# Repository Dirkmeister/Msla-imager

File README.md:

# Msla-imager

Shared code for the MSLA PCB imager (MSLA PRINTER Claude Project). This index is kept by HQ, in step with the Code home section of imager-00.

- **Folders.** Each folder belongs to one lane, except `calcs/`, where any lane adds its own calc scripts as separate files.
- **One writer per file.** The lane that creates a file owns it and names itself on line 1, or on line 2 under a shebang; other lanes change it through that owner.
- **Commits** start with the package or lane (`L4.2: loader`, `L4: converter v0`). A packet that confirms code cites the commit.

| Folder | Lane | What |
|---|---|---|
| `calcs/` | HQ, plus lane-owned scripts | `imager_calcs.py` (HQ, recovery pending). Lane scripts: `l1_*` (L1 Light engine), `l2_*` (L2 LCD mask) |
| `light/` | L1 Light engine | Cluster and sink board KiCad, stand mounts (not started) |
| `lcd/` | L2 LCD mask | Pi video config and bring-up scripts (`setup_display.sh`, `fbtest.py`, `show_png.py`, `edid_timing.py`; simulation-checked), the 1:1 PNG script until L4 takes it, package records in `lcd/records/` |
| `software/` | L4 Software | Pattern generator, Gerber-to-PNG converter, IF-13 job files; later the Pi app. See `software/README.md` |
| `firmware/` | L3 Controller and safety | Nano firmware (not started) |
| `mech/` | L5 Mechanics | Platen and enclosure CAD, 3018 G-code (not started) |

Plan docs live in the Claude Project (imager-00 to imager-09, IF-13 spec). Run L4 tools from `software/`. Datasheets under copyright (the Sharp LS055R1SX04 spec, for one) stay out of this repo.

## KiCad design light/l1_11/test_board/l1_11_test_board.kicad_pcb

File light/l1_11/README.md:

# L1: L1.11 C optic test: bench procedures, test board, rig

Package L1.11 of lane L1 (imager-09). Tests: T-UV-7 (optic 400 nm efficiency) and T-UV-6 (LED-to-optic height, beam, pointing), then C21 or C28 (imager-06 "C optic and array checks", calc §5 and §6c). This folder holds what the bench needs; the calc scripts and readings sit in `calcs/` (`l1_11_*`).

Rule for every step with a lit LED: the shroud is closed first. Read through the meter, never by eye in the beam (R9). The XL6009 check has no UV.

## 1. XL6009 bench check (no UV)

What it proves: the XL6009 module (B07XG323G8) holds 26.2 V at the C21 strings' 0.55 A from the 12 V brick for 10 min without running hot (calc §8). Readings go in `calcs/l1_11_xl6009.csv`; `python3 calcs/l1_11_xl6009.py` does the math and the pass rules.

On hand: XL6009 module, ALITOVE ALT-1205T brick, the two 24 Ω 50 W loads, Klein MM300 (one meter), Klein IR thermometer, leads.

```
 brick +12 ──(meter, 10 A jack, step 6 only)── IN+ ┌─────────┐ OUT+ ── 24 Ω ── 24 Ω ──┐
 brick GND ─────────────────────────────────── IN- │ XL6009  │ OUT- ──────────────────┘
                                                   └─────────┘
 loads screwed or clamped flat on metal; fingers off: 7.15 W each
```

1. **Cap.** Read the voltage printed on the output electrolytic (the OUT side). Pass: ≥ 35 V. → `cap_out_rating_V`.
2. **Load, cold.** Meter on 200 Ω: touch the probes together (`R_leads_ohm`), then the two loads in series (`R_load_cold_ohm`, about 48).
3. **Set point.** Brick on, no load. Meter on 200 V at OUT; trim the pot to read 26.2 (`V_out_noload_V`). Also note the brick alone on 20 V (`V_brick_noload_V`).
4. **Run.** Power off, connect the 48 Ω load (on metal), power on and start a timer. Meter stays in V mode; move the probes, not the wires:
   - 1 min: OUT on 200 V → `V_out_1min_V`. If it reads under 26.2, trim back to 26.2 now and log the trimmed value instead.
   - 2 min: IN terminals on 20 V → `V_in_2min_V`. 5 min OUT, 6 min IN, 10 min OUT and IN.
   - Watch for a dropout or the output clicking off → `dropout_or_hiccup`.
5. **Temperatures at 10 min.** IR thermometer close in, so the spot covers one part: XL6009 chip, diode, inductor, output cap, each load (the loads' shiny housing reads low: aim at a matte spot or a strip of masking tape). Room temperature at the bench. Pass: hottest module point ≤ 185 °F (85 °C) (EST, proposed).
6. **Input current.** Power off. Meter red lead to the 10 A jack, in series with IN+. Power on, read within 30 s while everything is still hot → `I_in_A`. Power off. Red lead back to the V jack before anything else.
7. Optional: the same in series with OUT+ → `I_out_A` (the script also gets it from V/R).

Expected (EST, calc §8): 0.546 A and 14.30 W out; about 1.40 A in at 12.0 V at 85 %. The meter's 10 A range is ±(3 % + 5 digits), so η comes out about ±0.07: good enough for the record, not a pass rule.

Pass (proposed; the lead confirms): cap ≥ 35 V; 26.2 V with no load; Vout at 10 min within 0.1 V of 1 min with no dropout; hottest module point ≤ 85 °C. A fail puts a CV boost on the buy list with the build optics.

## 2. Test board panel (`test_board/`)

One KiCad 7 file, three boards on one 2-sided 1.6 mm (0.063 in) 1 oz FR4 blank. Panel 86 x 125 mm (3.39 x 4.92 in). On a 4 x 5 in (101.6 x 127 mm) piece that leaves 0.31 in (7.8 mm) a side across but only 0.04 in (1 mm) a side along: (101.6 - 86)/2 and (127 - 125)/2. A 4 x 6 in (101.6 x 152.4 mm) piece leaves 0.54 in (13.7 mm) along for clamping; or cut the test board (86 x 80 mm) from one piece and the two small boards from another. Isolation-milled on the top only, 0.4 mm (15.7 mil) cuts; the bottom copper stays intact as a floating heat spreader. PCB milling on the 3018 isn't set up yet (Dallas, 2026-11-17): the Gerbers wait for it.

- `l1_11_test_board.kicad_pcb` / `.kicad_pro`, footprints in `l1_11.pretty` (project `fp-lib-table`). Regenerate: `python3 light/l1_11/test_board/make_test_board.py` (KiCad 7 pcbnew). No schematic: the board is drawn directly; nets below.
- `gerber/`: F.Cu (isolate), Edge.Cuts (cut out), PTH drill (10 x 0.126 in (3.2 mm), all unplated on a milled board), F.SilkS and F.Fab for reference. B.Cu is empty on purpose: don't mill the bottom.
- `drc_report.txt`: 0 clearance, short or unconnected errors. Left: library warnings (this sandbox has no global footprint table; they clear in your KiCad) and a few silkscreen warnings (no silk on a milled board).

**A. Test board, 86 x 80 mm (3.39 x 3.15 in).** 9 CUN0LF1B at C21's pitch, 0.787 x 0.893 in (20.00 x 22.68 mm), footprint `LED_SMD:LED_PLCC_2835_Handsoldering` (KiCad 7's stock part matches the V1 board @ 8208f05 pad for pad: large pad 1 = K at -1.05 mm, pad 2 = A at +1.525 mm). The strings are the rows, anode on the left: `VIN_Rr | D | Rr_N1 | D | Rr_N2 | D | Rr_OUT`. Each cut runs through an LED's pad gap, so every inner cathode pad sits in a 0.77 x 0.88 in (19.6 x 22.3 mm) island (119.325 - 99.725 by 111.14 - 88.86 for the center LED): most of the copper stays (L1.12 reads FR4's per-LED θ from this board). NTC TH1 (1206) sits on two isolated islands 0.20 in (5 mm) right of the center LED, beside its cathode pad, with two wire pads. No ballasts on this board: their 1.1 W typ would bias L1.12's θ. Holes: 4 x M3 on the ATS's 53.00 mm (2.087 in) square centred on the center LED, 4 x M3 on a 71.0 mm (2.795 in) square for the holder and the rig frame, so the board mounts at 0° or 90° for the two scan axes; each hole has an isolated copper ring under the screw head, so a screw can't join two nets through the ATS.

**B. Control board, 60 x 40 mm, outside the shroud.** Brick +12 V in → three VIN wires. Each string's OUT wire → a link (JP1-3: solder bridge, or clip lead; open it and clip the meter's 200 mA range across to read that string's current; leave it open to switch the string off) → ballast R1-3 → GND. Ballast footprint takes either your 12 Ω ≥ 0.61 W axial laid flat (leads bent to the outer pads) or four 47 Ω 1206 in parallel (11.75 Ω): fit one. Detector load RL across DET A+/K- (1206 or axial, 100 kΩ to start) with meter pads; NTC wire and meter pads.

**C. Detector board, 22 x 36 mm.** The spare CUN0LF1B (D10) as the detector, A+ and K- wire pads, 2 x M3 to the detector carriage.

**Before soldering: polarity.** The footprint (and V1) say the large pad is the cathode; the CUN0LF1B DS drawing isn't readable as text. Two checks, neither powers an LED:
1. Phone macro photos, sent here: a spare from the cut tape, top and bottom; one LED on the populated V1 board with both pads in view (V1 put pad 1 = K on the large pad).
2. Daylight, optional: a spare with fine wires on its pads, 1 MΩ across them, meter on 200 mV, facing a window or outside. A positive reading means the red lead is on the anode.

If the large pad turns out to be the anode, nothing changes on the board: all nine face the same way, so swap the string wires (VIN on the right pads, OUT on the left). The NTC still sits by the large (thermal) pad.

**Assembly.** LEDs from the cut tape, all the same way round (large pad right as drawn). Mill, deburr, clean; paste and hot air or a hot plate, or an iron. TH1 on its two islands; two fine wires off its wire pads, flat on the board, out past the right edge (the holder gets a groove for them). Grease on the ATS, board centred on it, 4 x M3 through the ATS's corner holes (caliper them first, and the ATS base thickness, for the screw length); nuts between the fins.

| Wire | From | To |
|---|---|---|
| VIN1-3 | control V12 pads | test board VIN1-3 (left edge) |
| OUT1-3 | test board OUT1-3 (right edge) | control S1-S3 OUT pads |
| NTC x2 | TH1 wire pads | control NTC pads |
| DET x2 | detector A+, K- | control DET A+, K- |
| Brick | +12 and GND | control +12 IN, GND IN |

At the brick's 12.0 V each string runs 125-225 mA across the Vf bins, 175 mA typ, through 12 Ω; ballast 0.61 W max (calcs/l1_c_lead_checks.py section 6, EST). With 4 x 47 Ω (11.75 Ω) the top bin reaches (12.0 - 3 x 3.1)/11.75 = 230 mA, still under the DS's 250 mA.

## 3. Rotation rig (`rig/`)

Dallas picked the turntable over the hand-moved slide (2026-11-17): the board turns under a knob on the shroud lid, the detector stays put, and the shroud never opens during a scan. The axis runs through the center optic's exit face. It replaces imager-06's linear detector scan (proposed to the lead in the packet).

`l1_11_rig.scad` (OpenSCAD 2021.01, parametric) → `sh export.sh` writes `stl/` (binary STL) and the picture. Every part fits the MK3S+ bed (250 x 210 x 210 mm); the largest is a track segment at 226 x 44 mm.

| Part | Qty | Filament | Notes |
|---|---|---|---|
| `base` | 1 | black PLA | 150 x 150 mm; pivot boss, sockets for track 1 |
| `rotor` | 1 | black PLA | Ø140 mm, rim ticks every 5°; nut traps underneath |
| `frame` | 1 | black PETG or ASA | holds the board on its 71.0 mm hole square at 0° or 90°; the ATS passes through; the top arm carries the shaft. Next to warm parts, so not PLA |
| `shaft` | 1 | any | 10 mm square, prints 6.30 in (160 mm): cut from the top end to L = box inside height + lid thickness − 99 mm |
| `knob` | 1 | any | pointer reaches the scale's ticks |
| `scale` | 1 | any | Ø140 mm, 1° ticks, labels every 10° from −170 to 180; tape it to the lid |
| `track1`, `track2` | 1 each | black PLA | dovetail rib, joined by dovetail tabs (no screws); mm from the axis engraved; detents at 4, 12 and 18 in |
| `carriage` | 1 | black PLA | rides the rib; lock screw into the detents; post for the detector board |

Black inside the shroud keeps stray UV off the detector. Prints: 0.2 mm layers, 3 perimeters, 20-30 % infill, no supports (the frame prints on its back face; the carriage upright).

**Hardware (M3, from stock; check the lengths you have):**
- Frame foot to rotor: 2 x M3 x 14, nuts in the rotor's underside. The screw tip must not stick out below the rotor.
- Board to frame: 4 x M3 x 10 with no holder (board + frame = 7.6 mm); longer once the holder goes on (its thickness comes with its drawing). Nuts in the frame's back face.
- Board to ATS: 4 x M3, length = 1.6 mm + the ATS base thickness + a nut (caliper the base).
- Shaft pin: 1 x M3 x 16 through the arm into the shaft. Knob set screw: 1 x M3 x 10.
- Carriage lock: 1 x M3 x 10 down into a detent. Detector board: 2 x M3 x 10.

**Assembly.** Base on the shroud floor. Rotor over the boss. Board plus ATS onto the frame (4 corner screws), frame onto the rotor through the foot slots: slide it until the center optic's exit face sits over the boss, then tighten. Shaft into the arm, pinned. Tracks into the base's sockets. Carriage on the rib from the far end, the detector board on its post facing the board. Lid on, knob on the shaft, set screw. With the board square to the track (rotor 0 tick at the base's index), turn the scale until the pointer reads 0 and tape it down.

**Shroud (yours to build: cardboard box or foam board).** Inside at least 24 x 12 x 8 in (610 x 305 x 203 mm): the rig runs from the base's back edge at -75 mm to the track's end at +495 mm, 570 mm, plus 10 mm at the back wall = 580 mm (22.8 in). Lid: one Ø1.42 in (36 mm) hole over the boss, 3.35 in (85 mm) from the back wall, centred across; the knob's skirt covers it. One small hole low in a side wall for the 10 wires. Matte black inside if you can: wall reflections show up as false tails in the profile. A background reading with the beam turned away (±150°) measures what's left.

**Waits for the optics.** The holder plate, the black blanks (they block a lit LED's pocket) and the 0.010 in (0.25 mm) shims. No public 20XPS drawing turned up (LEDSupply lists Ø20 x 8.5 mm only), so the holder gets drawn from calipers when they land. Measure on one optic: overall diameter and height; any rim or flange, its diameter and thickness; the bottom face diameter; the entrance cavity's diameter and depth; any legs or pins. Plus the height of a spare 3528 off the tape. A side-on and a bottom-up phone photo helps. The frame's foot slots take ±0.47 in (±12 mm) of exit-face height, so the holder can come out at whatever height the optic needs.

## 4. T-UV-7: optic efficiency at 400 nm (first; go/no-go)

Readings sheet: `calcs/l1_11_optic_readings.csv`, written in bench order by `python3 calcs/l1_11_optic_test.py --skeleton`, with every dial angle filled in. Fill only the `reading` column; `python3 calcs/l1_11_optic_test.py` does the rest (with no readings yet it runs its self-test on synthetic scans).

Method (proposed, replaces imager-06's linear scan): the board turns, the detector stays at D = 4.00 in (101.6 mm). Flux through the sphere about the axis, Φ = 2π D² ∫ E(φ) sin φ dφ, from the mean of four half-profiles (two axes, both sides). η = Φ_optic / Φ_bare, three passes. Both are integrated, so the bare LED doesn't need to be Lambertian.

1. **Setup.** Shroud closed for every reading. Detector wired to the control board's DET pads, RL = 100 kΩ across them, meter on 200 mV (2000 mV for the optic's peak). String 2 only: link S2 bridged, S1 and S3 open. That lights D4, D5 and D6; D5 is the center LED on the axis. During optic passes, D4 and D6 carry black blanks.
2. **Range check, once, before pass 1.** Optic on D5, dial at 0, LED settled (step 3). Pick RL so this peak reads 200-500 mV: start at 100 kΩ, go up if it's under 200, down if it's over 500. Above about 0.5 V the detector starts to forward-bias itself and stops being linear (EST). The bare LED then reads about 1/23 of the peak (the self-test's on-axis gain at 4 in), about 9-22 mV, still 90-220 counts on the 200 mV range. Keep that RL for the whole session: every result is a ratio.
3. **Settle.** After each power-up, wait until the on-axis reading holds within 1 % for a minute (EST 2-3 min) before scanning. Each scan starts with a dark reading (UV off).
4. **Scans** (the sheet lists every angle): bare from −85° to +85° every 5° (35 readings); optic every 1° to ±15°, 2.5° to ±40°, 5° to ±85° (69). Pass 1 does both axes (board at 0° then 90°), passes 2 and 3 the x axis: 416 readings.
5. **Result.** η ≥ 0.50 passes (EST, L1.3's low end). Under 0.50: stop and report (a UV-absorbing grade, or a poor fit on the 3528) before any T-UV-6 work.

The plans' interpolation bias on η, checked on synthetic scans: −0.04 % optic (log-linear), −0.07 % bare (linear, 5° steps). Wide angles matter more than they look, because the sin φ weight grows with angle. In the self-test's beam (15° core plus 3 % of the peak in a 50° wide tail), 14.7 % of the flux lies beyond ±21.5°, where the intensity is only 2.1 % of the peak, and 3.9 % beyond ±40° at 0.51 %. A scan stopping at ±21.5° would read η about 15 % low on that beam.

## 5. T-UV-6: height, beam, profile, pointing

1. **Height.** D = 12 in (304.8 mm), x axis, holder seated then raised 0.010 in (0.25 mm) at a time: 0, 0.25, 0.50, 0.75 mm (add 1.00 if 0.75 is still the narrowest). Each scan: on axis plus every 1° from 4° to 12° each side (19 readings). The narrowest FWHM sets the height; record it, board to optic base.
2. **Far field.** At the set height: 18 in on x, then 12 and 18 in on y (board at 90°). FWHM = 2 atan((D₂ tan φ₂ − D₁ tan φ₁)/(D₂ − D₁)) from the half-max angles φ; the difference takes out the 0.79 in (20 mm) aperture.
3. **Profile.** At the set height, 12 in, both axes: every 0.5° to ±10°, 1° to ±20°, 2.5° to ±40° (77 readings each). Gives the flux outside ±7.5° and ±15°, and the 10-90 % edge half-width at the resist (calc §5), for t = 0.0128 and 0.0285 in (0.326, 0.725 mm) until T-LCD-4 measures t. A Gaussian of 15° FWHM gives 1.22 and 2.71 mil; the script's 2D rebuild reproduces both to 0.002 mil.
4. **Pointing.** Each LED alone: its optic on, blanks on its two row-mates, its row's link bridged. 7 readings 3° apart around where its beam should land, −atan(s/D) on the dial for an LED s off the axis (±3.76° for ±0.787 in (20 mm) at 12 in). The script shift-fits the step 3 profile to them and corrects the parallax. Board at 0° for x, 90° for y: 126 readings.
5. **Background.** Once per session: the beam turned to ±150° (away from the detector), one reading. That's the box's stray light; if it's over 1 % of the peak, blacken the walls before trusting the tails.

**Bench time (EST):** T-UV-7 416 readings, T-UV-6 413, about 10 s a reading with the knob, plus about 3 min per shroud opening (holder swaps, board turns, blanks): about 1.5 h for T-UV-7 and 2.5 h for T-UV-6. Two sittings in this thread.

**C21 or C28.** The script calls it: C21 if η ≥ 0.50 and the edge half-width ≤ 2.5 mil (REQ-008) at the governing t; if it holds only at the thin t, C21 rests on T-LCD-4. Build optics for C21: 21 + 4 spares − 9 reusable test optics = 16, about $26.36 before shipping at LEDSupply's 2026-11-17 listing (EST; confirm at order).

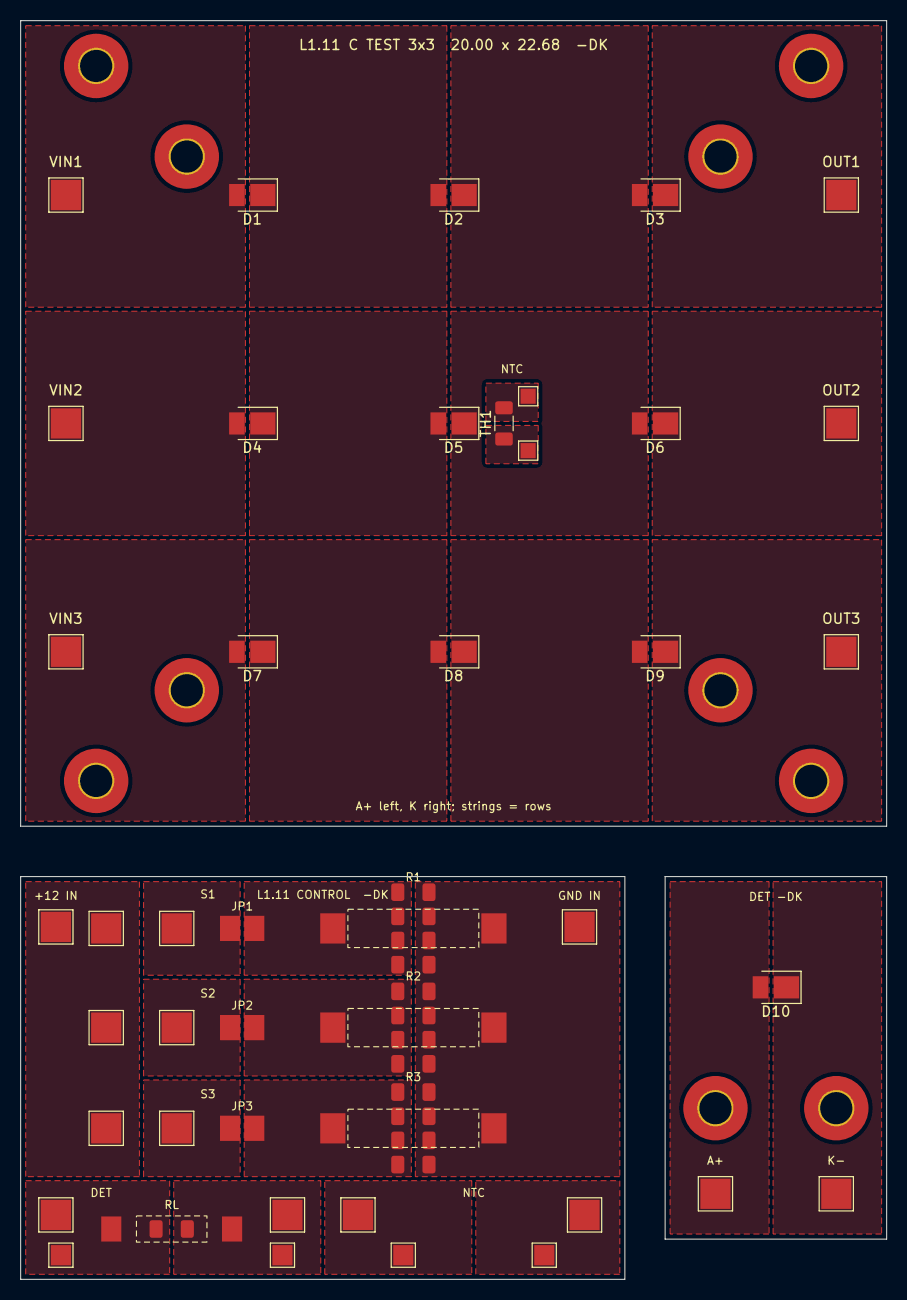
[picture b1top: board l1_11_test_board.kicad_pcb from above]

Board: 2 copper layers, 86.0 x 125.0 mm, 54 parts (0 on the bottom side), 28 nets, no tracks yet.

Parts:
D1, D2, D3, D4, D5, D6, D7, D8, D9: CUN0LF1B; LED_PLCC_2835_Handsoldering
D10: CUN0LF1B (detector); LED_PLCC_2835_Handsoldering
H1, H2, H3, H4, H5, H6, H7, H8, H9, H10: M3; MountingHole_3.2mm_M3_Pad_TopOnly
JP1: S1 link / meter; Link_2Pad_Gap0.4mm
JP2: S2 link / meter; Link_2Pad_Gap0.4mm
JP3: S3 link / meter; Link_2Pad_Gap0.4mm
R1, R2, R3: 12R axial >=0.61W | 4x47R 1206; Ballast_Axial_P16_or_4x1206
RL: 100k detector load (1206 or axial); R_1206_or_Axial_P12
TH1: B57621C5103K062 10k NTC; R_1206_3216Metric_Pad1.30x1.75mm_HandSolder
TP1: VIN_R1; TestPoint_Pad_3.0x3.0mm
TP2: VIN_R2; TestPoint_Pad_3.0x3.0mm
TP3: VIN_R3; TestPoint_Pad_3.0x3.0mm
TP4: OUT_R1; TestPoint_Pad_3.0x3.0mm
TP5: OUT_R2; TestPoint_Pad_3.0x3.0mm
TP6: OUT_R3; TestPoint_Pad_3.0x3.0mm
TP7: NTC_A wire; TestPoint_Pad_1.5x1.5mm
TP8: NTC_B wire; TestPoint_Pad_1.5x1.5mm
TP11: +12 IN; TestPoint_Pad_3.0x3.0mm
TP12: GND IN; TestPoint_Pad_3.0x3.0mm
TP13: VIN1 out; TestPoint_Pad_3.0x3.0mm
TP14: VIN2 out; TestPoint_Pad_3.0x3.0mm
TP15: VIN3 out; TestPoint_Pad_3.0x3.0mm
TP16: OUT1 in; TestPoint_Pad_3.0x3.0mm
TP17: OUT2 in; TestPoint_Pad_3.0x3.0mm
TP18: OUT3 in; TestPoint_Pad_3.0x3.0mm
TP21: DET A+ wire; TestPoint_Pad_3.0x3.0mm
TP22: DET K- wire; TestPoint_Pad_3.0x3.0mm
TP23, TP24: NTC wire; TestPoint_Pad_3.0x3.0mm
TP25: meter V+; TestPoint_Pad_2.0x2.0mm
TP26: meter COM; TestPoint_Pad_2.0x2.0mm
TP27, TP28: meter; TestPoint_Pad_2.0x2.0mm
TP31: A+ wire; TestPoint_Pad_3.0x3.0mm
TP32: K- wire; TestPoint_Pad_3.0x3.0mm

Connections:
DETB_A: D10.2, TP31.1
DETB_K: D10.1, TP32.1
DET_N: RL.2, TP22.1, TP26.1
DET_P: RL.1, TP21.1, TP25.1
GND: R1.2, R2.2, R3.2, TP12.1
LINK1_A: JP1.1, TP16.1
LINK1_B: JP1.2, R1.1
LINK2_A: JP2.1, TP17.1
LINK2_B: JP2.2, R2.1
LINK3_A: JP3.1, TP18.1
LINK3_B: JP3.2, R3.1
NTC_A: TH1.2, TP7.1
NTC_A_CTL: TP23.1, TP27.1
NTC_B: TH1.1, TP8.1
NTC_B_CTL: TP24.1, TP28.1
R1_N1: D1.1, D2.2
R1_N2: D2.1, D3.2
R1_OUT: D3.1, TP4.1
R2_N1: D4.1, D5.2
R2_N2: D5.1, D6.2
R2_OUT: D6.1, TP5.1
R3_N1: D7.1, D8.2
R3_N2: D8.1, D9.2
R3_OUT: D9.1, TP6.1
V12: TP11.1, TP13.1, TP14.1, TP15.1
VIN_R1: D1.2, TP1.1
VIN_R2: D4.2, TP2.1
VIN_R3: D7.2, TP3.1
